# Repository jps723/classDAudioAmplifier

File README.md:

# Class D Amplifier Build Notes 4/26/20

This project is in partnership with [Bantam Tools](https://www.bantamtools.com)

**Design Notes:**

This amplifier uses the [TPA3122](https://www.ti.com/lit/ds/symlink/tpa3122d2.pdf) IC to do the heavy lifting.  It is a stereo class D amp that is capable of driving up to 15w per channel.  In this circuit it is designed for 4Ω speakers in a stereo configuration.

At a high level, the circuit takes an input signal and converts it into a high-frequency square wave.  The high frequencies are then filtered out using an LC lowpass filter leaving the amplified version of the original signal to be transmitted to the speakers.  

The circuit operates on 12v with pins 1 and 10 supplying power to the Left and Right channels internal H-bridges. These are not powered internally by the AVCC pins which are powered separately on pins 16  and 17.  The shutdown pin is connected to 12v and mute is connected to ground as the circuit doesn’t include external controls.  The ‘Left In’ and ‘Right In’ pins are connected to a 3.5mm input jack through 1uF caps for filtering out the low frequencies of the input signal.   

Other notable connections are on Pins 14 and 15 which are used to set the overall gain of the amplifier.  The TPA3122 allows for 4 configurations as outlined in the table below.  The circuit is currently configured for a gain of 26 dB however could easily be adjusted within the schematic for a lower/higher gain.  

Pins 12 and 19 emit the Left and Right signals and are followed by an LC filter and coupling capacitor.
The circuit is designed in a 4 ohm, Single Ended (SE) configuration with the LC filter spec’d according to the datasheet for optimal performance.   

# **Milling Process**

**Top Layer:** The top layer only serves to add labeling.  If they’re not desired, this can be skipped.
Bits: 1/32”
Mill Time: ~2 ½ mins

**Bottom Layer:**
Bits: 1/32”
Mill Time: ~7 ½ mins

# **Build Process**

It’s easiest to solder the board in the following order:

```
1.	SMD Components
2.	Dip Socket
3.	Audio Jack
4.	Barrel Jack
5.	Screw Terminals
6.	Inductors
7.	Electrolytic Caps
```

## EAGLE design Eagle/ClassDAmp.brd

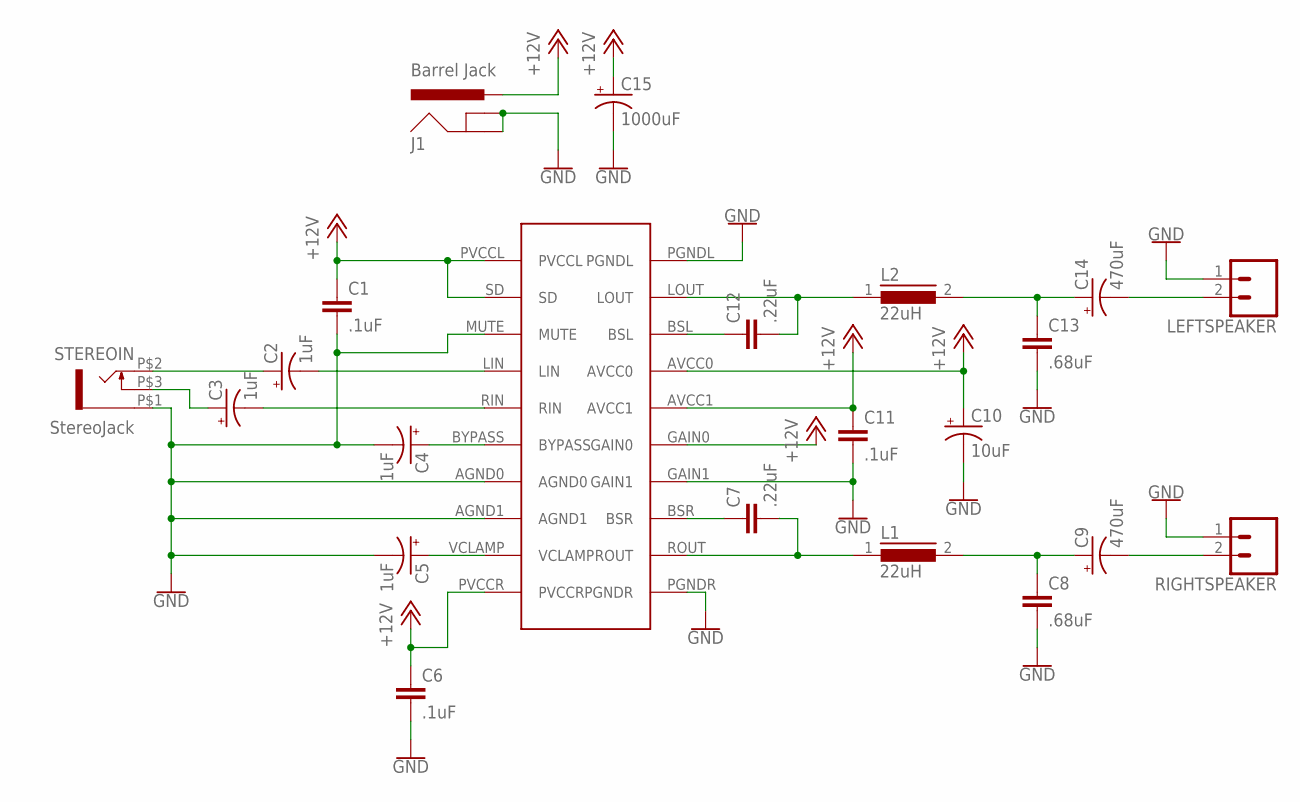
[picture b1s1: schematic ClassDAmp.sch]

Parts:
C1, C6, C11: .1uF; 0805
C2, C3, C4, C5: 1uF; CPOL-RADIAL-2.5MM-6.5MM
C7, C12: .22uF; 0805
C8, C13: .68uF; 0805
C9, C14: 470uF; CPOL-RADIAL-2.5MM-6.5MM
C10: 10uF; CPOL-RADIAL-2.5MM-6.5MM
C15: 1000uF; CPOL-RADIAL-2.5MM-6.5MM
J1: Barrel Jack; POWER_JACK_PTH_BREAD
L1, L2: 22uH; 82114R
LEFTSPEAKER: CONN_023.5MM; SCREWTERMINAL-3.5MM-2
RIGHTSPEAKER: CONN_023.5MM; SCREWTERMINAL-3.5MM-2
STEREOIN: StereoJack; HORIZONTAL_STEREO_JACK
U$1: TPA3122

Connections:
+12V: C1.1, C6.1, C10.1 (+), C11.1, C15.1 (+), J1.PWR, U$1.AVCC0, U$1.AVCC1, U$1.GAIN0, U$1.PVCCL, U$1.PVCCR, U$1.SD
GND: C1.2, C4.2 (-), C5.2 (-), C6.2, C8.2, C10.2 (-), C11.2, C13.2, C15.2 (-), J1.GND, J1.GNDBREAK, LEFTSPEAKER.1, RIGHTSPEAKER.1, STEREOIN.P$1 (1), U$1.AGND0, U$1.AGND1, U$1.GAIN1, U$1.MUTE, U$1.PGNDL, U$1.PGNDR
unnamed: C2.1 (+), STEREOIN.P$2 (2)
unnamed: C3.1 (+), STEREOIN.P$3 (3)
unnamed: C2.2 (-), U$1.LIN
unnamed: C3.2 (-), U$1.RIN
unnamed: C4.1 (+), U$1.BYPASS
unnamed: C7.1, U$1.BSR
unnamed: C5.1 (+), U$1.VCLAMP
unnamed: C7.2, L1.1, U$1.ROUT
unnamed: C14.2 (-), LEFTSPEAKER.2
unnamed: C8.1, C9.1 (+), L1.2
unnamed: C9.2 (-), RIGHTSPEAKER.2
unnamed: C12.1, U$1.BSL
unnamed: C12.2, L2.1, U$1.LOUT
unnamed: C13.1, C14.1 (+), L2.2

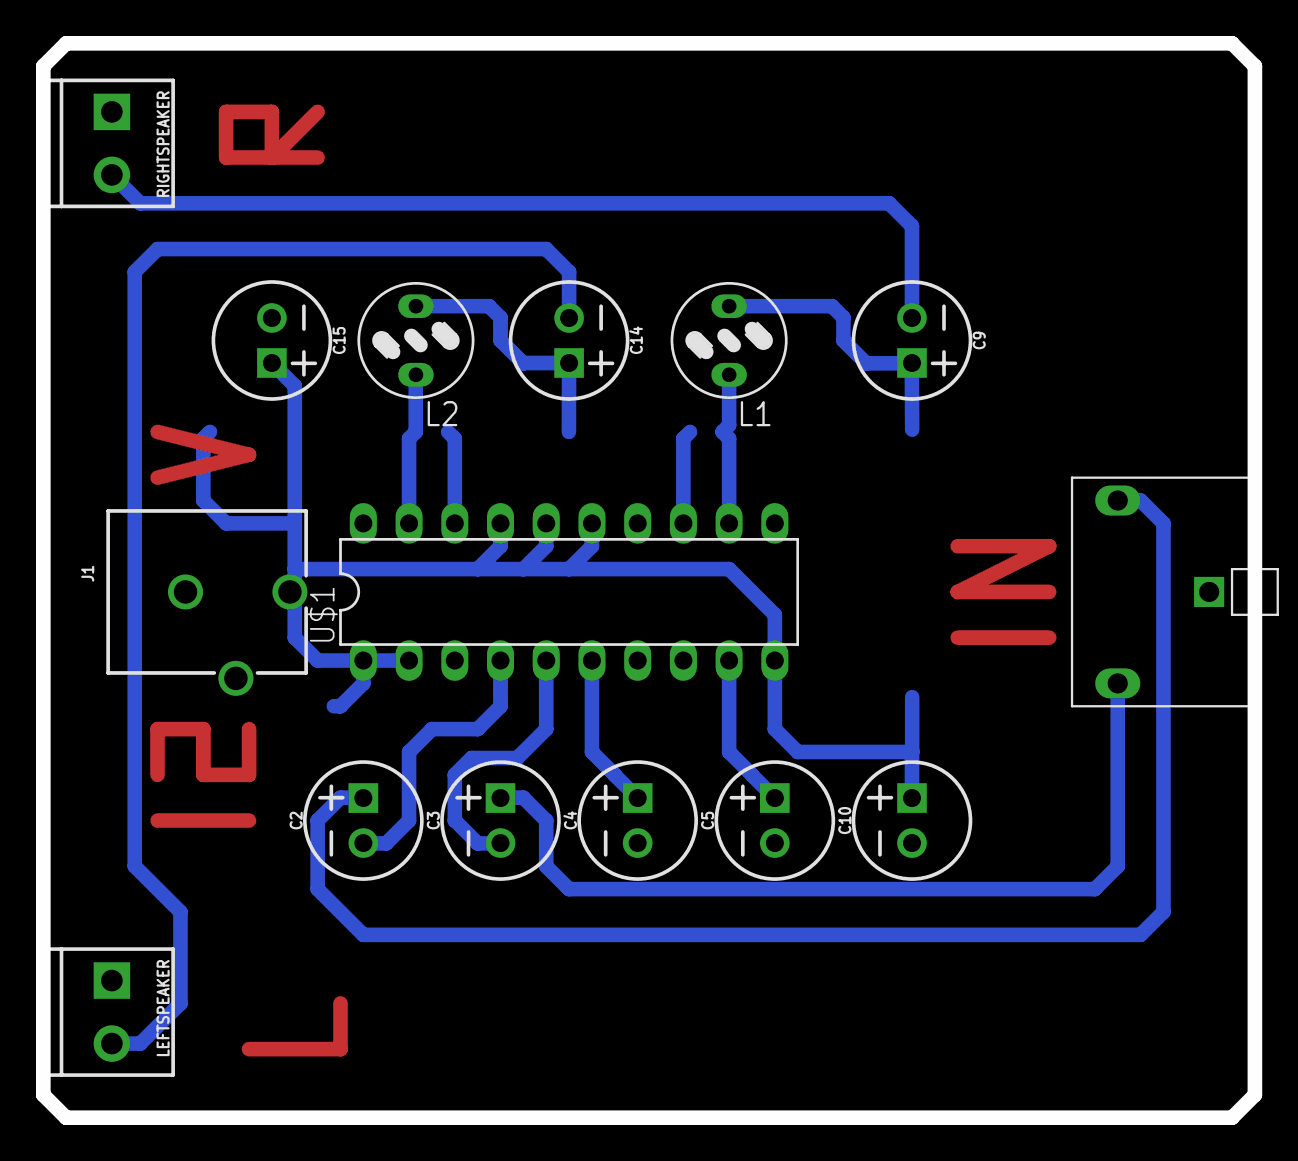
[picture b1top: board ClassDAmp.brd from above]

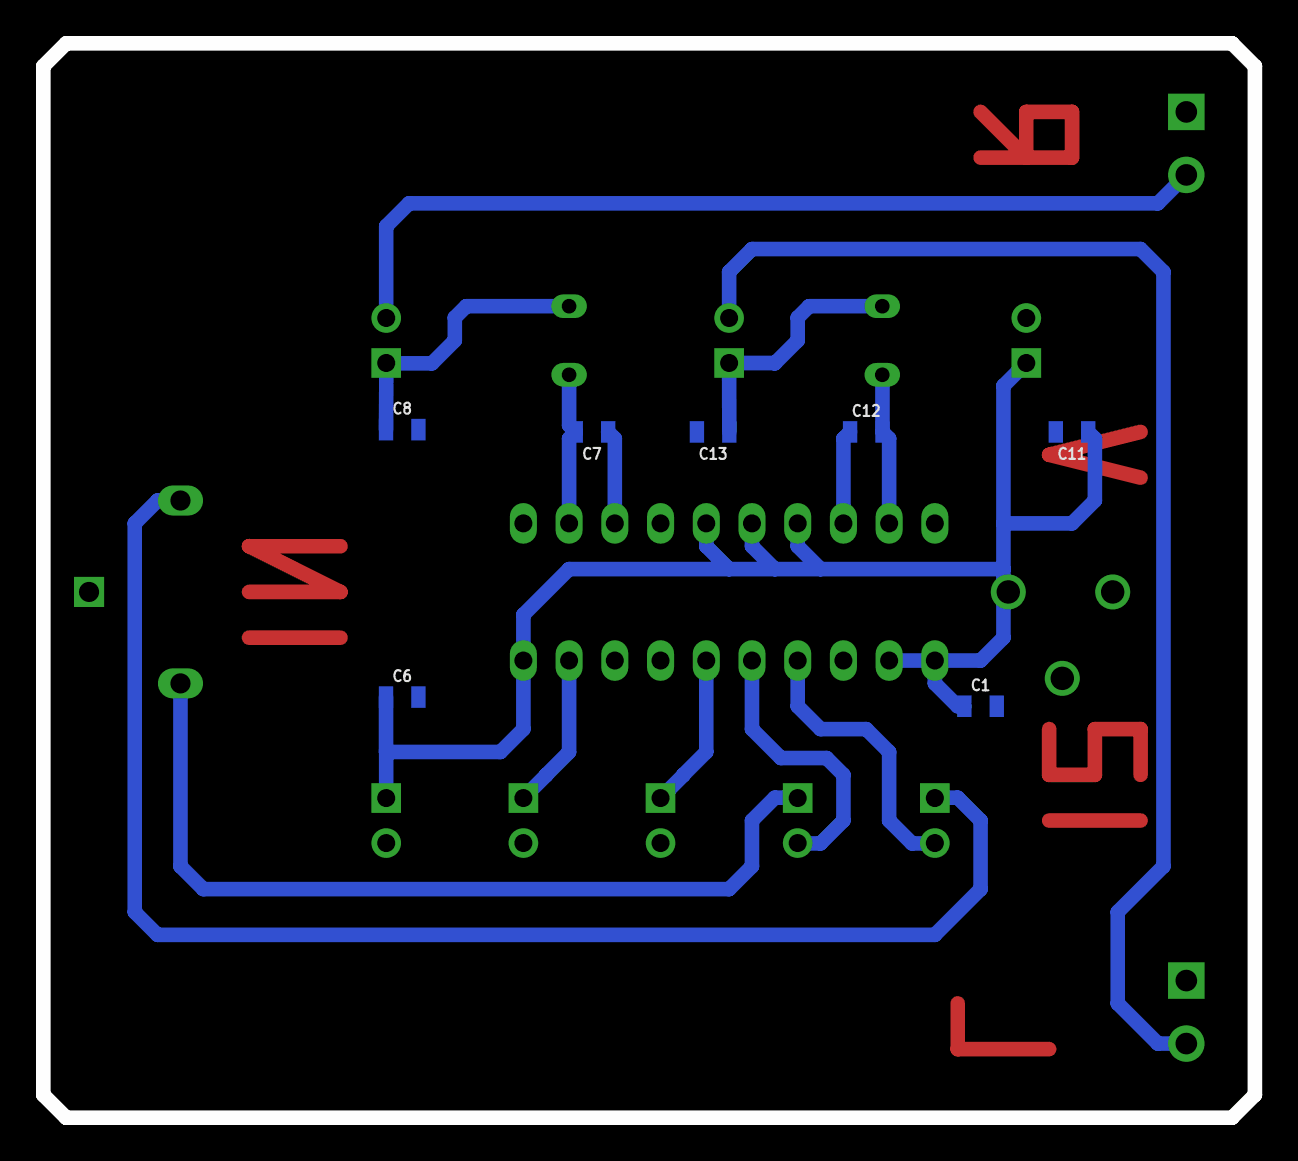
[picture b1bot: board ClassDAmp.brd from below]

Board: 2 copper layers, 67.3 x 59.7 mm, 22 parts (7 on the bottom side), 16 nets.

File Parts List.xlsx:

Part | Quantity | Notes
TPA3122 | 1.0 | DIP-20
Dip Socket | 1.0 | DIP-20
Horizontal Stereo Jack | 1.0 | Footprint: https://www.amazon.com/gp/product/B008SNZUYC/ref=ppx_yo_dt_b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
Barrel Jack | 1.0
22uH inductor | 2.0
Screw Terminaal | 2.0 | 2x1 .1" pitch
Capacitors
1000uF | 3.0 | Polar electrolytic
10uF | 1.0 | Polar electrolytic
1uF | 4.0 | Polar electrolytic
.68uF | 2.0 | SMD 0805
.22uF | 2.0 | SMD 0805
.1uF | 3.0 | SMD 0805

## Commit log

2020-10-28 deleted history file
2020-10-30 added bantam tools credit
2020-12-14 added .gitignore

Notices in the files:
parts and their libraries:
SparkFun-Capacitors: Licensing: Creative Commons ShareAlike 4.0 International - https://creativecommons.org/licenses/by-sa/4.0
